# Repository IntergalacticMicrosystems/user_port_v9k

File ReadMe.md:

# IntergalacticMicrosystems NOTE:
Will be tweaking this to use plain pico board and USB stdio.

# Victor 9000 User Port SD Card Interface

## Overview

This project enables the Victor 9000 to interface with an SD card via the User Port using a Raspberry Pi Pico. The Pico acts as a bridge between the Victor 9000 and the SD card, allowing MS-DOS 3.1 to read and write files as if it were a standard storage device.

The project consists of:
- 	A custom PCB that connects a Raspberry Pi Pico to the Victor 9000 User Port.
- 	A DOS device driver for MS-DOS 3.1 on the Victor 9000.
- 	Firmware for the Raspberry Pi Pico to handle SD card operations.

⸻

Features
- 	Read and write FAT16/FAT32 formatted SD cards.
- 	Accessible as a drive letter under MS-DOS 3.1.
- 	Uses the Victor 9000 User Port for communication.
- 	Low power consumption – powered directly from the user port.

⸻

Hardware Requirements

Required Components
- 	Victor 9000 running MS-DOS 3.1.
- 	Custom PCB
- 	Raspberry Pi Pico.
- 	SD card slot.
- 	SD card formatted as FAT16 or FAT32.

See the schamtic for Victor 9000 User Port to Raspberry Pi Pico Pin Mapping

⸻

Software Installation

1. Flash the Raspberry Pi Pico Firmware
    1. Connect your Pico to a PC via USB.
    1. Hold the BOOTSEL button and power on the Pico.
    1. Drag-and-drop the compiled firmware (user_port_pico.uf2) onto the RPI-RP2 drive.

1. Install the MS-DOS Device Driver
    1.	Copy the Victor 9000 DOS driver (SDDRV.SYS) to the system drive.
    1.	Edit CONFIG.SYS to include: `DEVICE=userport.sys`

1.	Reboot the Victor 9000.

⸻

Usage

Accessing the SD Card

Once the driver is loaded, the SD card will be assigned a drive letter (e.g., E:). You can then use standard DOS commands:

DIR E:\
COPY C:\FILE.TXT E:\
DEL E:\OLD.TXT

Formatting an SD Card

The SD card must be formatted with FAT16 or FAT32. Use a modern PC to format the card before inserting it into the Victor 9000. You'll also need a Victor formatted disk image loaded on the card.

⸻

Troubleshooting

Driver Not Loading
 - Ensure userport.sys is in the root of your boot disk
 - Check CONFIG.SYS syntax.
 - Verify the Victor 9000 User Port connection.

SD Card Not Detected
 - Ensure the SD card is FAT16/FAT32 formatted.
 - Check the Pico firmware is flashed correctly.
 - Verify the Victor 9000 User Port wiring.
## Credits
 - Hardware & Software Development: Paul Devine
- Many thanks to profdc9 at the VCFED forums who provided the code that got me started you can find it here:
[ https://forum.vcfed.org/index.php?threads/ms-dos-driver-for-an-sd-card-connected-via-a-parallel-port.41516/](url)
- Many thanks to Educardo Casino for his Openwatcom DOS driver [https://github.com/eduardocasino/dos-device-driver](url) which I incorported.
- Victor 9000 Background info and help: Many thanks to Bitsavers, Disk Blitz and the folks at the AppleSauce discord for patiently explaining to me lots of background; FozzTexx for his help in understanding some of the Victor 9000 hardware; FreddyV, Polpo, and the folks at the Retro Pico discord for letting me lurk over their shoulders; and Intergalactic for finding the hard disk struct documentation!

For questions or contributions, feel free to open an issue or submit a pull request.

I'm releasing this under the GPL-v2 as the source code I've incorporated utilized that licensing scheme.

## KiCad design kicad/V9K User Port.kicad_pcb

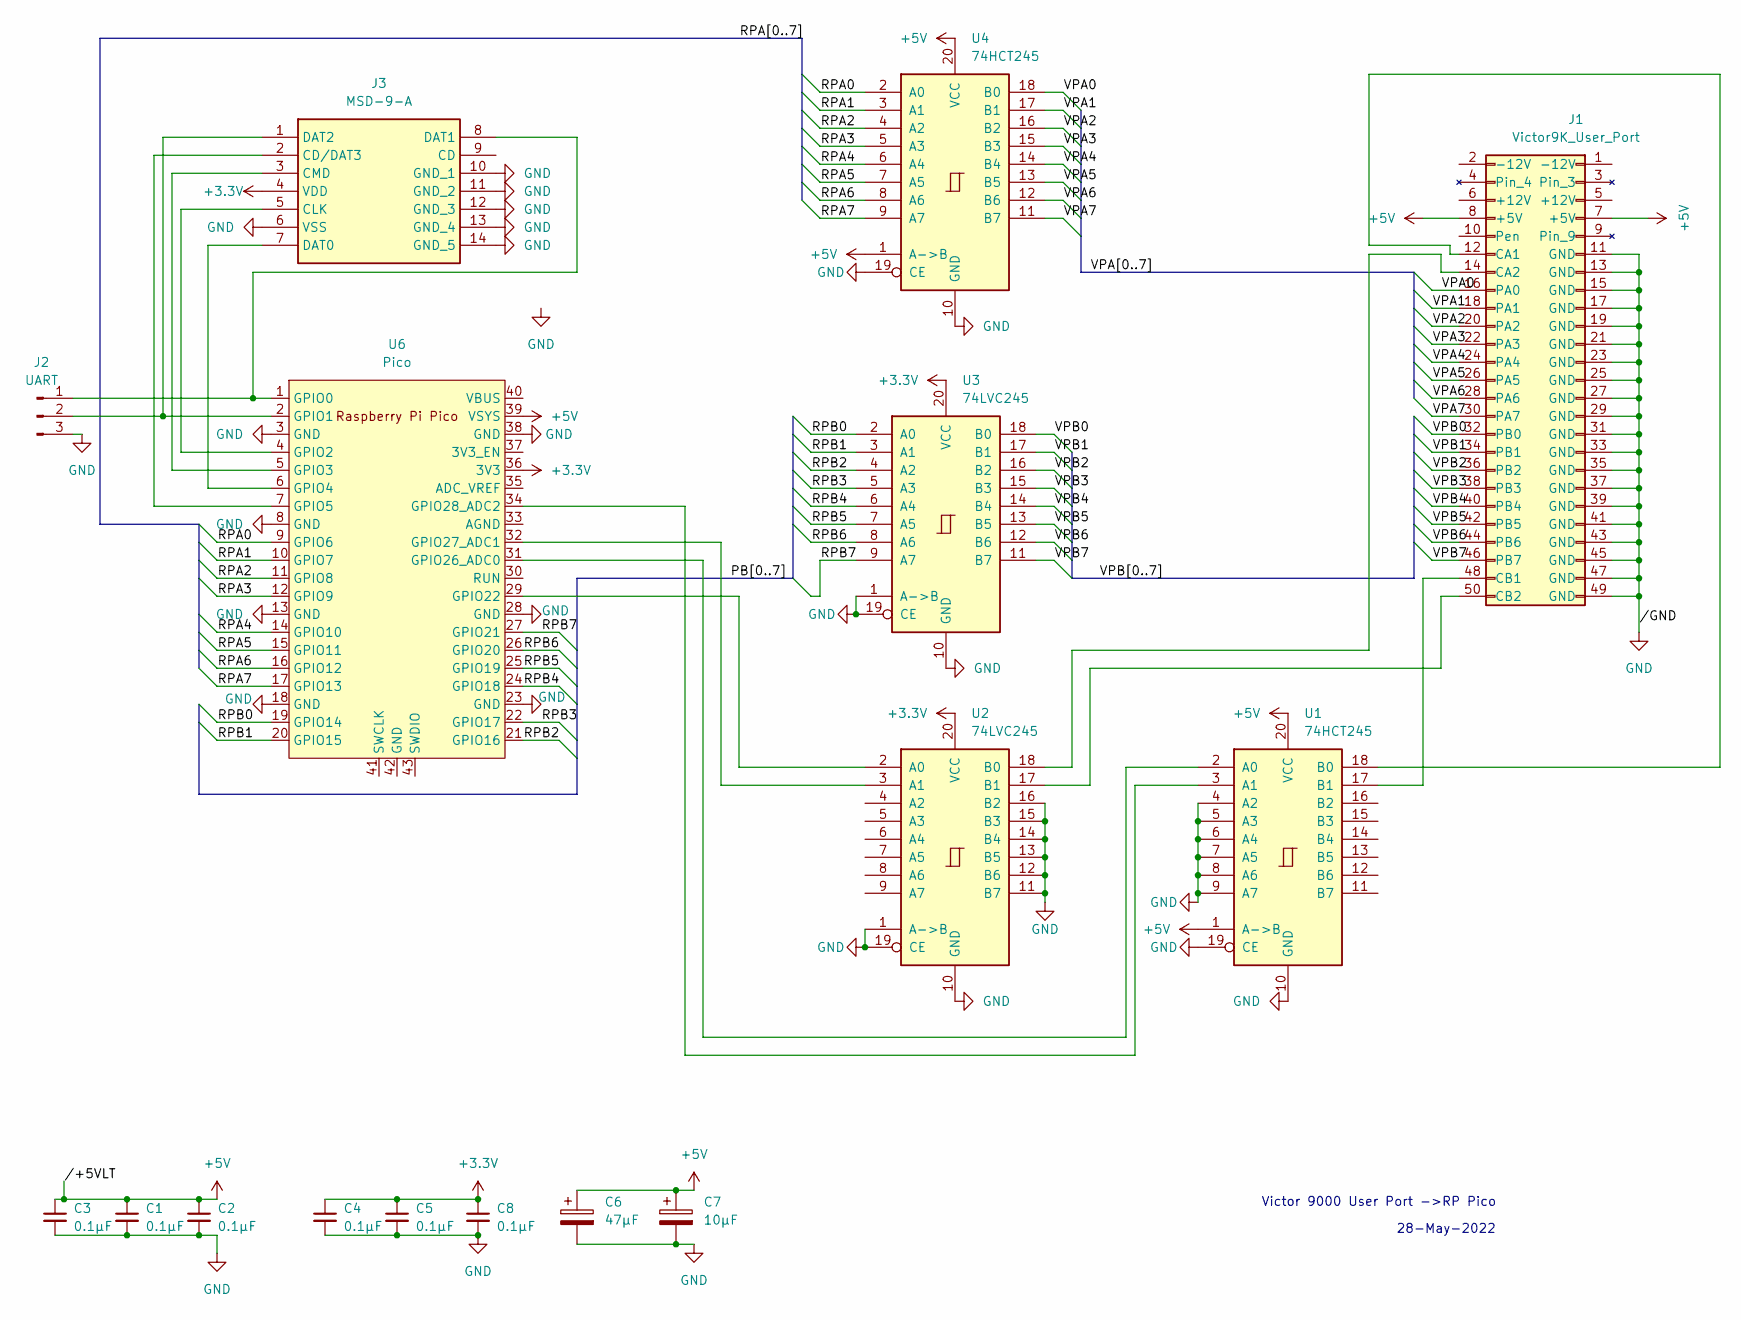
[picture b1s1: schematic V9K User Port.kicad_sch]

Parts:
C1, C2, C3, C4, C5, C8: 0.1µF; C_Disc_D3.0mm_W1.6mm_P2.50mm
C6: 47µF; CP_Radial_D5.0mm_P2.50mm
C7: 10µF; CP_Radial_D5.0mm_P2.50mm
J1: Victor9K_User_Port; PinHeader_2x25_P2.54mm_Vertical
J2: UART; PinHeader_1x03_P2.54mm_Vertical
J3: MSD-9-A; MSD9A; Manufacturer_Part_Number MSD-9-A
U1, U4: 74HCT245; DIP-20_W7.62mm
U2, U3: 74LVC245; DIP-20_W7.62mm
U6: Pico; RPi_Pico_SMD_TH

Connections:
+3.3V: C4.1, C5.1, C8.1, J3.4 (VDD), U2.20 (VCC), U3.20 (VCC), U6.36 (3V3)
+5V: C1.1, C2.1, C3.1, C6.1, C7.1, J1.7 (+5V), J1.8 (+5V), U1.1 (A->B), U1.20 (VCC), U4.1 (A->B), U4.20 (VCC), U6.39 (VSYS)
/RPA0: U4.2 (A0), U6.9 (GPIO6)
/RPA1: U4.3 (A1), U6.10 (GPIO7)
/RPA2: U4.4 (A2), U6.11 (GPIO8)
/RPA3: U4.5 (A3), U6.12 (GPIO9)
/RPA4: U4.6 (A4), U6.14 (GPIO10)
/RPA5: U4.7 (A5), U6.15 (GPIO11)
/RPA6: U4.8 (A6), U6.16 (GPIO12)
/RPA7: U4.9 (A7), U6.17 (GPIO13)
/RPB0: U3.2 (A0), U6.19 (GPIO14)
/RPB1: U3.3 (A1), U6.20 (GPIO15)
/RPB2: U3.4 (A2), U6.21 (GPIO16)
/RPB3: U3.5 (A3), U6.22 (GPIO17)
/RPB4: U3.6 (A4), U6.24 (GPIO18)
/RPB5: U3.7 (A5), U6.25 (GPIO19)
/RPB6: U3.8 (A6), U6.26 (GPIO20)
/RPB7: U3.9 (A7), U6.27 (GPIO21)
/VPA0: J1.16 (PA0), U4.18 (B0)
/VPA1: J1.18 (PA1), U4.17 (B1)
/VPA2: J1.20 (PA2), U4.16 (B2)
/VPA3: J1.22 (PA3), U4.15 (B3)
/VPA4: J1.24 (PA4), U4.14 (B4)
/VPA5: J1.26 (PA5), U4.13 (B5)
/VPA6: J1.28 (PA6), U4.12 (B6)
/VPA7: J1.30 (PA7), U4.11 (B7)
/VPB0: J1.32 (PB0), U3.18 (B0)
/VPB1: J1.34 (PB1), U3.17 (B1)
/VPB2: J1.36 (PB2), U3.16 (B2)
/VPB3: J1.38 (PB3), U3.15 (B3)
/VPB4: J1.40 (PB4), U3.14 (B4)
/VPB5: J1.42 (PB5), U3.13 (B5)
/VPB6: J1.44 (PB6), U3.12 (B6)
/VPB7: J1.46 (PB7), U3.11 (B7)
GND: C1.2, C2.2, C3.2, C4.2, C5.2, C6.2, C7.2, C8.2, J1.11 (GND), J1.13 (GND), J1.15 (GND), J1.17 (GND), J1.19 (GND), J1.21 (GND), J1.23 (GND), J1.25 (GND), J1.27 (GND), J1.29 (GND), J1.31 (GND), J1.33 (GND), J1.35 (GND), J1.37 (GND), J1.39 (GND), J1.41 (GND), J1.43 (GND), J1.45 (GND), J1.47 (GND), J1.49 (GND), J2.3, J3.6 (VSS), J3.10 (GND_1), J3.11 (GND_2), J3.12 (GND_3), J3.13 (GND_4), J3.14 (GND_5), U1.4 (A2), U1.5 (A3), U1.6 (A4), U1.7 (A5), U1.8 (A6), U1.9 (A7), U1.10 (GND), U1.19 (CE), U2.1 (A->B), U2.10 (GND), U2.11 (B7), U2.12 (B6), U2.13 (B5), U2.14 (B4), U2.15 (B3), U2.16 (B2), U2.19 (CE), U3.1 (A->B), U3.10 (GND), U3.19 (CE), U4.10 (GND), U4.19 (CE), U6.3 (GND), U6.8 (GND), U6.13 (GND), U6.18 (GND), U6.23 (GND), U6.28 (GND), U6.38 (GND)
unnamed: J1.12 (CA1), U1.18 (B0)
unnamed: J1.14 (CA2), U2.18 (B0)
unnamed: J1.48 (CB1), U1.17 (B1)
unnamed: J1.50 (CB2), U2.17 (B1)
unnamed: J2.1, J3.8 (DAT1), U6.1 (GPIO0)
unnamed: J2.2, J3.1 (DAT2), U6.2 (GPIO1)
unnamed: J3.2 (CD/DAT3), U6.7 (GPIO5)
unnamed: J3.5 (CLK), U6.4 (GPIO2)
unnamed: J3.3 (CMD), U6.5 (GPIO3)
unnamed: J3.7 (DAT0), U6.6 (GPIO4)
unnamed: U1.2 (A0), U6.31 (GPIO26_ADC0)
unnamed: U1.3 (A1), U6.34 (GPIO28_ADC2)
unnamed: U2.2 (A0), U6.29 (GPIO22)
unnamed: U2.3 (A1), U6.32 (GPIO27_ADC1)

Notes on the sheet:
Victor 9000 User Port ->RP Pico
28-May-2022

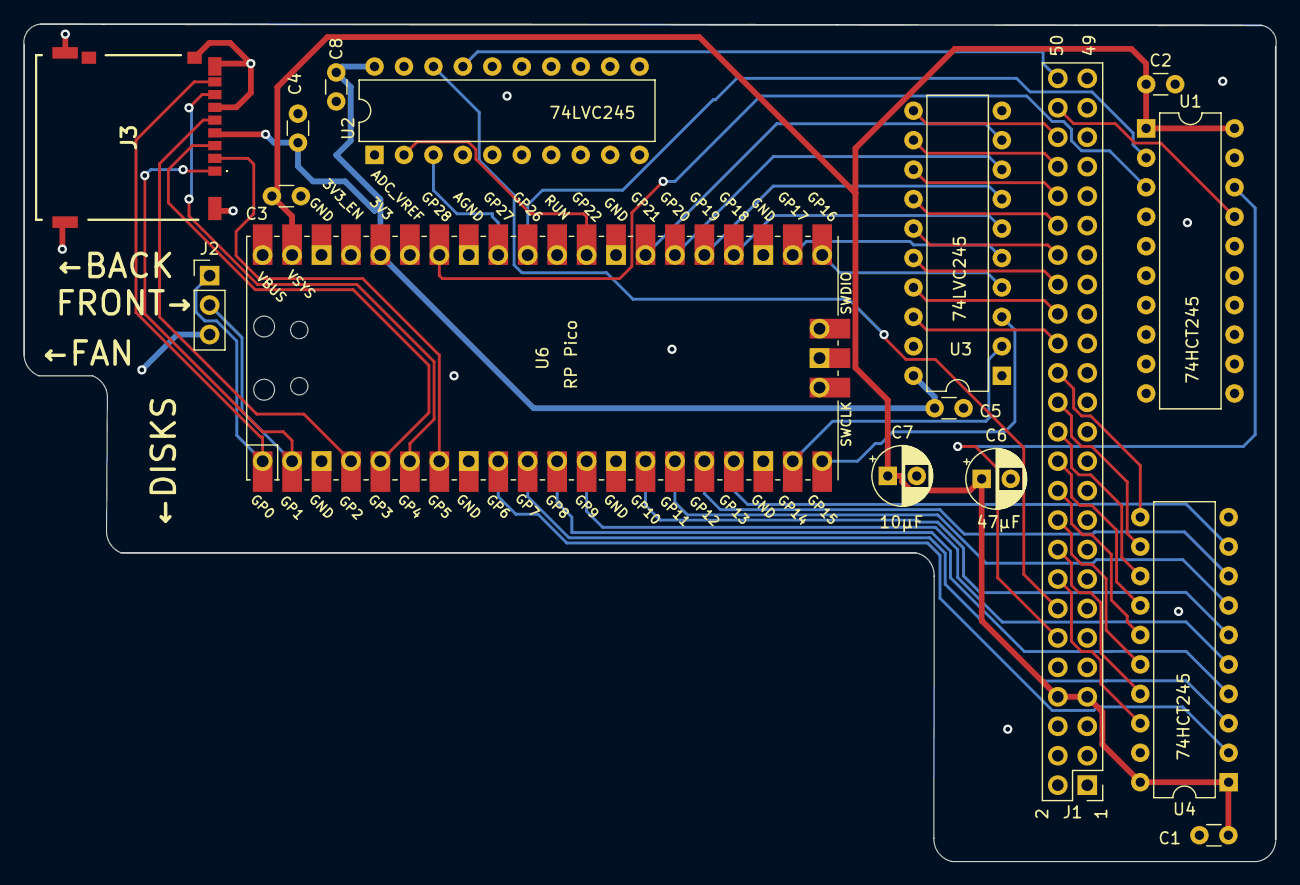
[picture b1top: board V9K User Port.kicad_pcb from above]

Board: 4 copper layers, 108.0 x 72.2 mm, 16 parts (0 on the bottom side), 49 nets.

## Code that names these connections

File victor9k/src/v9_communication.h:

#include "../../common/protocols.h"

#ifndef _USER_PORT_H
#define _USER_PORT_H

#pragma pack(push, 1)
// Serial port control registers
#define INTEL_DEV_SEGMENT 0xE000      // Base address segment for UART control, 7201 serial controller
#define NEC7201_REG_OFFSET 0x0040     // Base address offset for UART control, 7201 serial controller
#define NEC7201_RESET_CMD 0x18        // Channel reset command for the 7201 serial controller in hex
#define NEC7201_CHAR_AVAILABLE 0x01   // Bit mask for character available in 7201 status register
#define NEC7201_TX_BUFFER_EMPTY 0x04  // Bit mask for TX buffer empty in 7201 status register

// Timer control registers, used to control baud rate
#define TIMER_8253_OFFSET 0x0020 // Timer base address offset for baud rate setup
#define CLOCK_8253_FREQUENCY 1250000 // 1.25MHz clock frequency

// Segment for 8259 programable interrupt controller [PIC] used for interrupt handling
#define PIC_8259_OFFSET 0x0000
#define PIC_NON_SPECIFIC_EOI  0x20   //Mask for End of Interrupt
#define PIC_VIA_SPECIFIC_EOI 0x62   //Mask for End of Interrupt

// Constants for setting up the interrupt service routine
#define INTERRUPT_NUM 0x43
#define IVT_ENTRY (INTERRUPT_NUM * 4) // Each Interrupt Vector Table [IVT] entry is 4 bytes


// The keyboard VIA, resgister 1, is located at E804:0001. The appropriate bits are:
//   Bit 0 (PA0) for port A
//   Bit 1 (PAl) for port B
// Thus,bysettingPA0 to zero,the internal clock is enabled for port A;
// setting PA1 to zero will enable the internal clock for port B.
// Setting PA0 or PAl to one will enable the external disabling the internal clock.
#define PHASE2_DEVICE_SEGMENT 0xE800
#define VIA1_REG_OFFSET   0x0020    // via1 for centronics parallel port   
#define VIA2_REG_OFFSET   0x0040    // via2 keyboard, serial params, parallel enable
#define VIA3_REG_OFFSET   0x0080    // via3 user port, GPIO pins on motherboard
#define TALK_ENABLE_H     0x01      // patallel talk-enable line line VIA2 PB0
#define INTERNAL_EXT_A    0x01      // PAO INT/EXTA Serial A internal / external clock select (LOW=INT)
#define INTERNAL_EXT_B    0x02      // PA1 INT/EXTB Serial B internal / external clock select (LOW=INT)
#define SERIAL_A_RING_IND 0x03      // PA2 RIA Serial A ring indicator (J8-22)
#define SERIAL_A_DSR      0x04      // PA3 DSRA Serial A data set ready (J8-6)
#define SERIAL_B_RING_IND 0x05      // PA4 RIB Serial B ring indicator (J9-22)
#define SERIAL_B_DSR      0x06      // PA5 DSRB Serial B data set ready (J9-6)

// Constants for Handshake configuration
#define VIA_PULSE_MODE         0xAA   // Setup CA / CB as pulse lines for read/write
#define VIA_HANDSHAKE_MODE     0x88   // Setup CA / CB as handshake lines for read/write

// Constants for setting up the Shift Register [SR] and interrupts
#define SR_RESET_MODE          0xE3  // Bit mask to clear the SR mode bits
#define SHIFT_OUT_MODE_110     0x18  // Shift out with mode 110
#define SR_INTERRUPT_MASK      0x04  // Bit to enable SR interrupts in int_enable_reg

//Constants for overall 6522 interactions
#define CA1_INTERRUPT_MASK     0x02  // Bit to enable CA1 interrupts in int_enable_reg
#define CA2_INTERRUPT_MASK     0x01  // Bit to enable CA2 interrupts in int_enable_reg
#define CB1_INTERRUPT_MASK     0x10  // Bit to enable CB1 interrupts in int_enable_reg
#define CB2_INTERRUPT_MASK     0x04  // Bit to enable CB2 interrupts in int_enable_reg
#define CA1_CB1_BOTH_INTERRUPT 0x12  // Bit pattern to enable both CA1 and CB1 interrupts for handshake
#define INTERRUPT_ENABLE       0x80  // Bit in the int_enable_reg to turn on interrupts 
#define VIA_CLEAR_INTERRUPTS   0x7F  // Bit pattern to clear entire interrupt register
#define VIA_RESET_AUX_CTL      0x03  // Resets T1/T2/SR disabled, PA/PB latching enabled
#define MAX_POLLING_ITERATIONS 5000  // Maximum number of iterations to poll for interrupt
#define MAX_HANDSHAKE_ATTEMPTS 100   // Maximum number of handshake attempts before timeout

enum ports {PARALLEL, SERIAL_A, SERIAL_B, USER_PORT};


typedef struct {
    uint8_t out_in_reg_b;
    uint8_t out_in_reg_a;
    uint8_t data_dir_reg_b;         // data-direction, reg 'b'
    uint8_t data_dir_reg_a;
    uint8_t timer1_ctr_lo;
    uint8_t timer1_ctr_hi;
    uint8_t timer1_latch_lo;
    uint8_t timer1_latch_hi;
    uint8_t timer2_ctr_lo;
    uint8_t timer2_ctr_hi;
    uint8_t shift_reg;
    uint8_t aux_ctrl_reg;           // auxiliary Ctrl reg
    uint8_t periph_ctrl_reg;
    uint8_t int_flag_reg;           // interrupt flag register
    uint8_t int_enable_reg;         // interrupt enable register
    uint8_t out_in_reg_a_no_hs;     // out-in reg 'a' NO HANDSHAKE
} V9kParallelPort;

/* something about our makefile isn't letting these be linked, defining here */
extern void Enable( void );
#pragma aux Enable = \
    "sti" \
    parm [] \
    modify [];
extern void Disable( void );
#pragma aux Disable = \
    "cli" \
    parm [] \
    modify [];

static void delay_us(unsigned int n);
#pragma aux delay_us = \
    "mov cx, ax", \
    "loopit:", \
    "loop loopit", \
    parm [ax] \
    modify [cx];

#pragma pack( pop )

ResponseStatus initialize_user_port(void);
void interrupt far userPortISR(void);
ResponseStatus send_startup_handshake(void);
ResponseStatus send_uint16_t(uint16_t data);
ResponseStatus sendBytes(uint8_t far *data, size_t length);
ResponseStatus receiveBytes(uint8_t far *data, size_t length);
ResponseStatus send_command_payload(Payload *payload);
ResponseStatus send_command(Payload *command);
ResponseStatus receive_response(Payload *response);
ResponseStatus send_command_packet(Payload *payload);
ResponseStatus send_data_packet(Payload *payload);

#endif

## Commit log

2024-05-20 starting to build out protocol and organize existing files
2024-05-20 deleting submodule to try and fix it
2024-05-20 added submodule for sdio-fatfs
2024-05-24 initial build version
2024-05-25 clearly separating pico dependencies from common code
2024-05-25 additional cleanup of pico code separated from common
2024-05-25 build script for integrating openwatcom compile on a macos and cmake which don't play nice together
2024-05-25 build config for openwatcom and cmake on macos
2024-05-25 initial version
2024-06-22 bootstrapping a bunch of the build and testing
2024-06-30 creating test directory, moving major code to a library that's testable
2024-06-30 remove sdio so can add as a git module
2024-06-30 add no-OS-FatFS-SD-SDIO-SPI-RPi-Pico as submodule
2024-06-30 moving test out of pico in order to change c compilter to native one instead of cross compiling pico
2024-06-30 moving Unity into test folder
2024-09-25 updated CMakeLists for pico 2.0 SDK and pimorono pico plus 2
2024-09-25 working SDIO setup on pimoroni rp2354
2024-09-25 added .h file to move UART to 32,33 pins
2024-10-05 added more debug output in PIO code
2024-10-13 rewrote protocol to make memory allocation simpler, as well as resuse for request and response
2024-10-13 removed duplicate pico sdk setups from cmakelists
2024-10-13 filtered out macos . files from valid entries
2024-10-13 pulled latest update to SDIO-FATFS
2024-10-15 started flushing out the victor side of the communication path
2024-10-20 refining pico->v9 communication channel, getting BPB plumbed correctly.
2024-10-29 added debugging to CRC calcs
2024-10-29 cleaned up protocol behavior
2024-10-29 changed device name to userport
2024-10-29 cleaned up bpb_table pointer
2024-10-29 removed a bunch of cruft from when I was testing the basic hardware
2024-10-29 cleaning up legacy code in template file
2024-10-29 removing cruft .pio files, they are in the lib dir now
2024-10-29 cleaning up protocol after testing with Victor hardware
2024-10-29 removing failed attempt at automated tests
2024-10-29 fixing uint16_t CRC8 calculation overflow
2024-10-29 removing print each value
2024-10-30 added missing pragma pack, cleaned up Payload organization, removed wcc compiliation warnings, removed SD card cruft from parallel port
2024-10-30 removing legacy parallel port from makefile
2024-10-30 fixed pragma pack issue
2024-10-30 added read_burst_from_pio method
2024-10-30 pulled in latest sdio-fatfs
2024-10-31 V9 receive CRC wasn't waiting for DATA_READY
2024-10-31 cleaned up duplicate handshake logging
2024-10-31 made init response payload explicit, fixed bug in param passing address not value
2024-10-31 removing attempt to print data payload
2024-10-31 fixed pointer reference error
2024-10-31 cleaned up logging
2024-10-31 removed mistaken validation on response parsing"
2024-10-31 fixed attempt to write to null pointer
2024-10-31 added MBR offset, had been trying to find partition where MBR sits
2024-10-31 updated references to bpb pointer
2024-10-31 added vcopy to compilation step
2024-11-01 attempt at cleaning up bpb array so less confusing what's going on
2024-11-02 read command that uses a buffer for storing the data
2024-11-02 renamed volume_id to drive_number
2024-11-02 cleaned up sd_read method
2024-11-03 initial stab at read() and write() functions
2024-11-04 added more debug statements
2024-11-06 testing if debug output is corrupting stack
2024-11-09 fixing debug across two platforms
2024-11-09 first ramdrive version that reads dir cleanly
2024-11-09 first ramdrive version that worked for reading and writing. was returning a near * for buildBpb() when I should have been returning a far*. was causing stack corruption.
2024-11-10 moved the ramdrive stuff behind an ifdef
2024-11-10 removing drive_num from device header, not present in V9K
2024-11-10 cleaned up memory sanity checks
2024-11-16 cleaning up far pointers on data segment
2024-11-16 fixing offset of read write within disk structure, fixing MBR reading
2024-11-16 fixing MBR handling, starting in on V9K HD structs
2024-11-17 continued evolution of V9K disk images
2024-11-17 cleaned up BPB fields for victor's expectations. first version to show directory structure and read, write cleanly.
2024-11-25 added initial classes to log things to pico console instead of to victor display
2024-11-25 swapping over a bunch of V9K display output to log on pico
2024-11-25 adding support for V9K formatted hard drives
2024-11-28 moved bpb output logging to pico to make debugging easier
2024-11-28 removed VirtualPartitionEntry as it made the data structure needlessly complex
2024-12-05 added additional logging
2024-12-14 updated openwatcom compiler to latest version, some paths moved
2024-12-14 cleaned up logging to debug write corruption
2024-12-14 upgraded sdio-fatfs library to latest version
2024-12-16 removing volume ID from data structures, the Victor code doesn't have that.
2024-12-16 creating a local variable to receive the responsePayload.data 0x0 response instead of corrupting the memory I had been handed as a buffer space.
2025-01-05 moved welcome message to std DOS interrupt function
2025-03-14 cleaning up debug output
2025-03-14 adding license and initial readme
2025-03-14 adding Schematica and PCB
2025-03-15 adding kicad files
2025-05-31 adj for plain pico + USB stdio
